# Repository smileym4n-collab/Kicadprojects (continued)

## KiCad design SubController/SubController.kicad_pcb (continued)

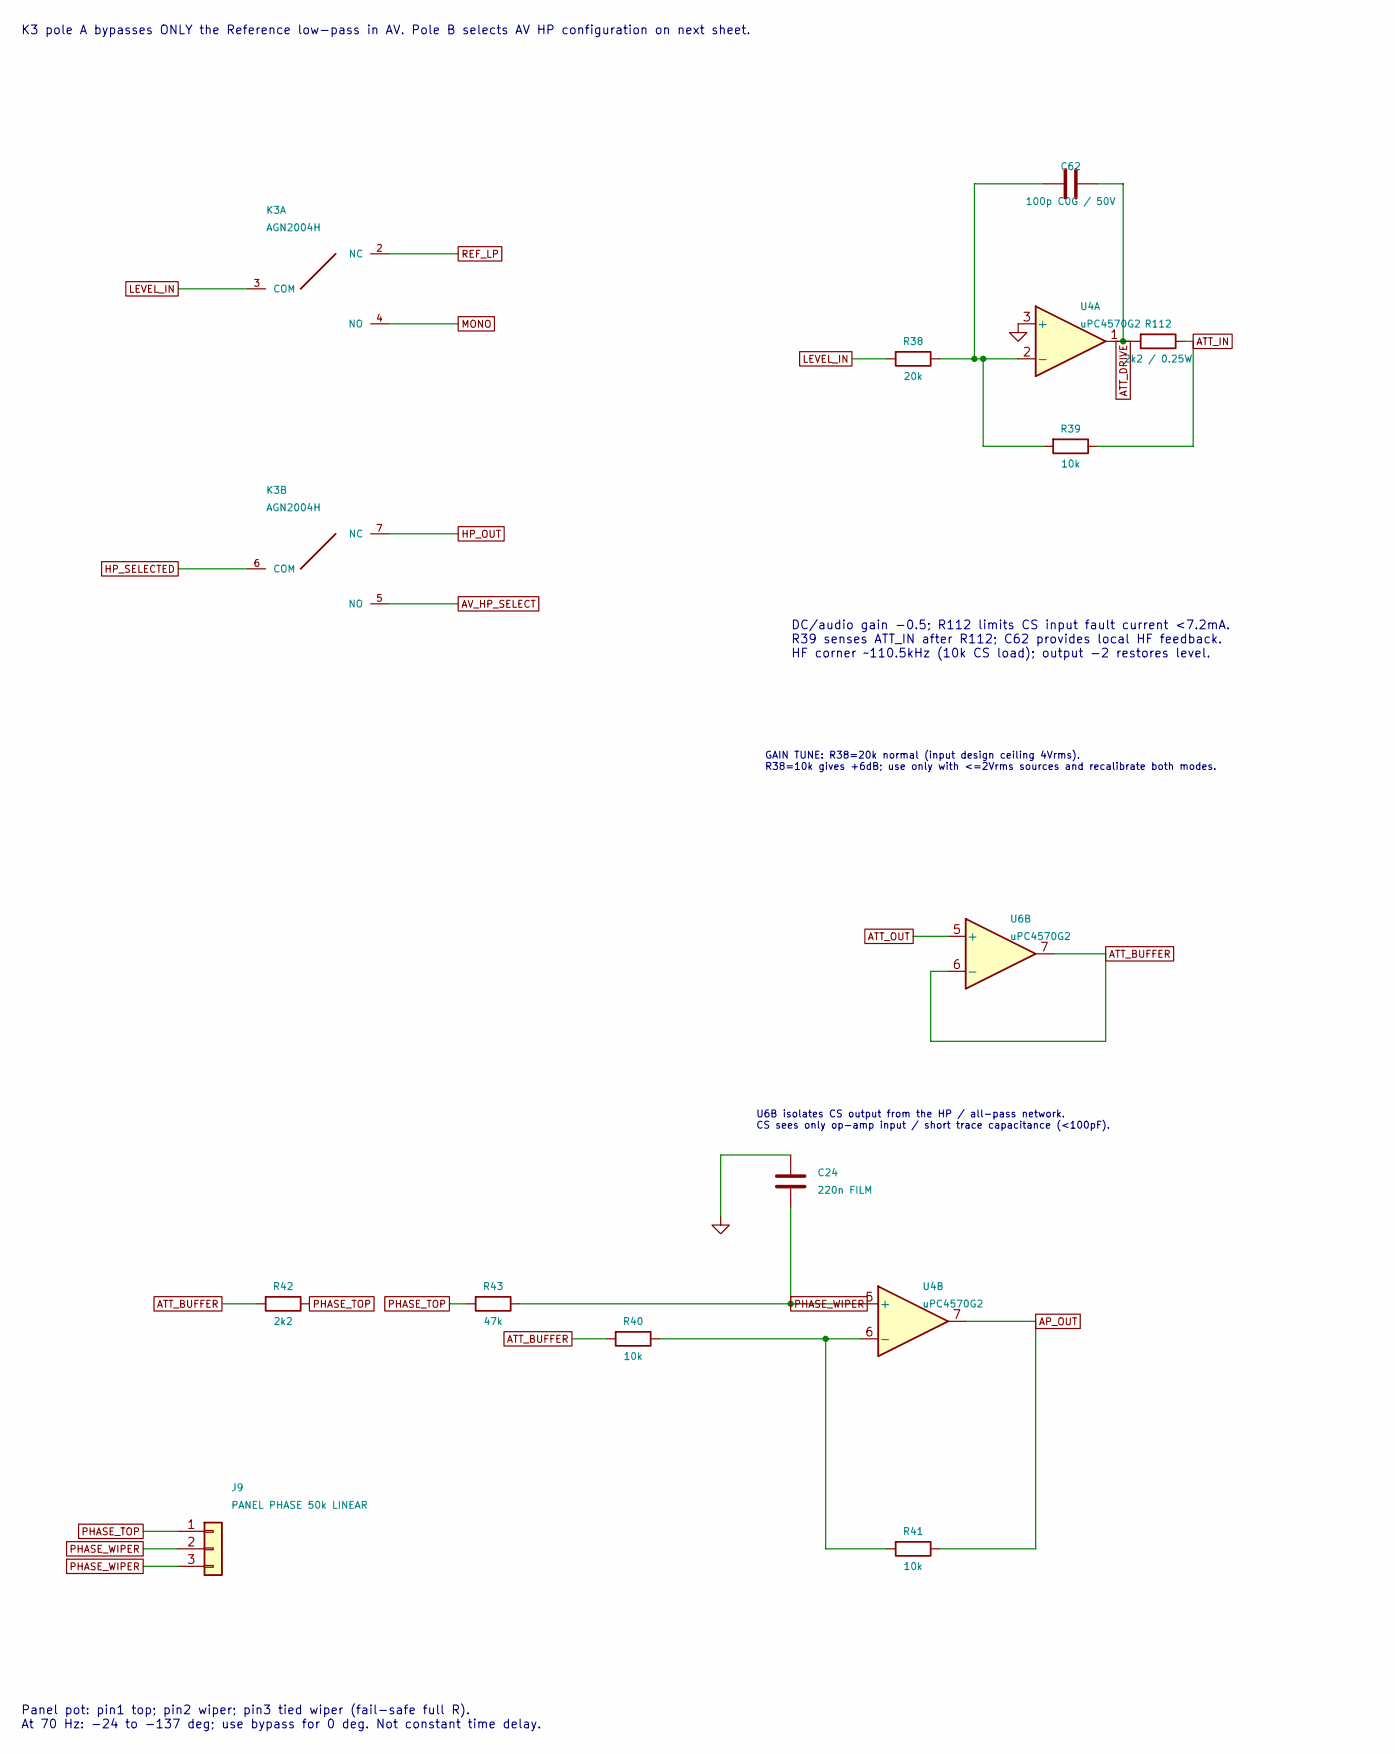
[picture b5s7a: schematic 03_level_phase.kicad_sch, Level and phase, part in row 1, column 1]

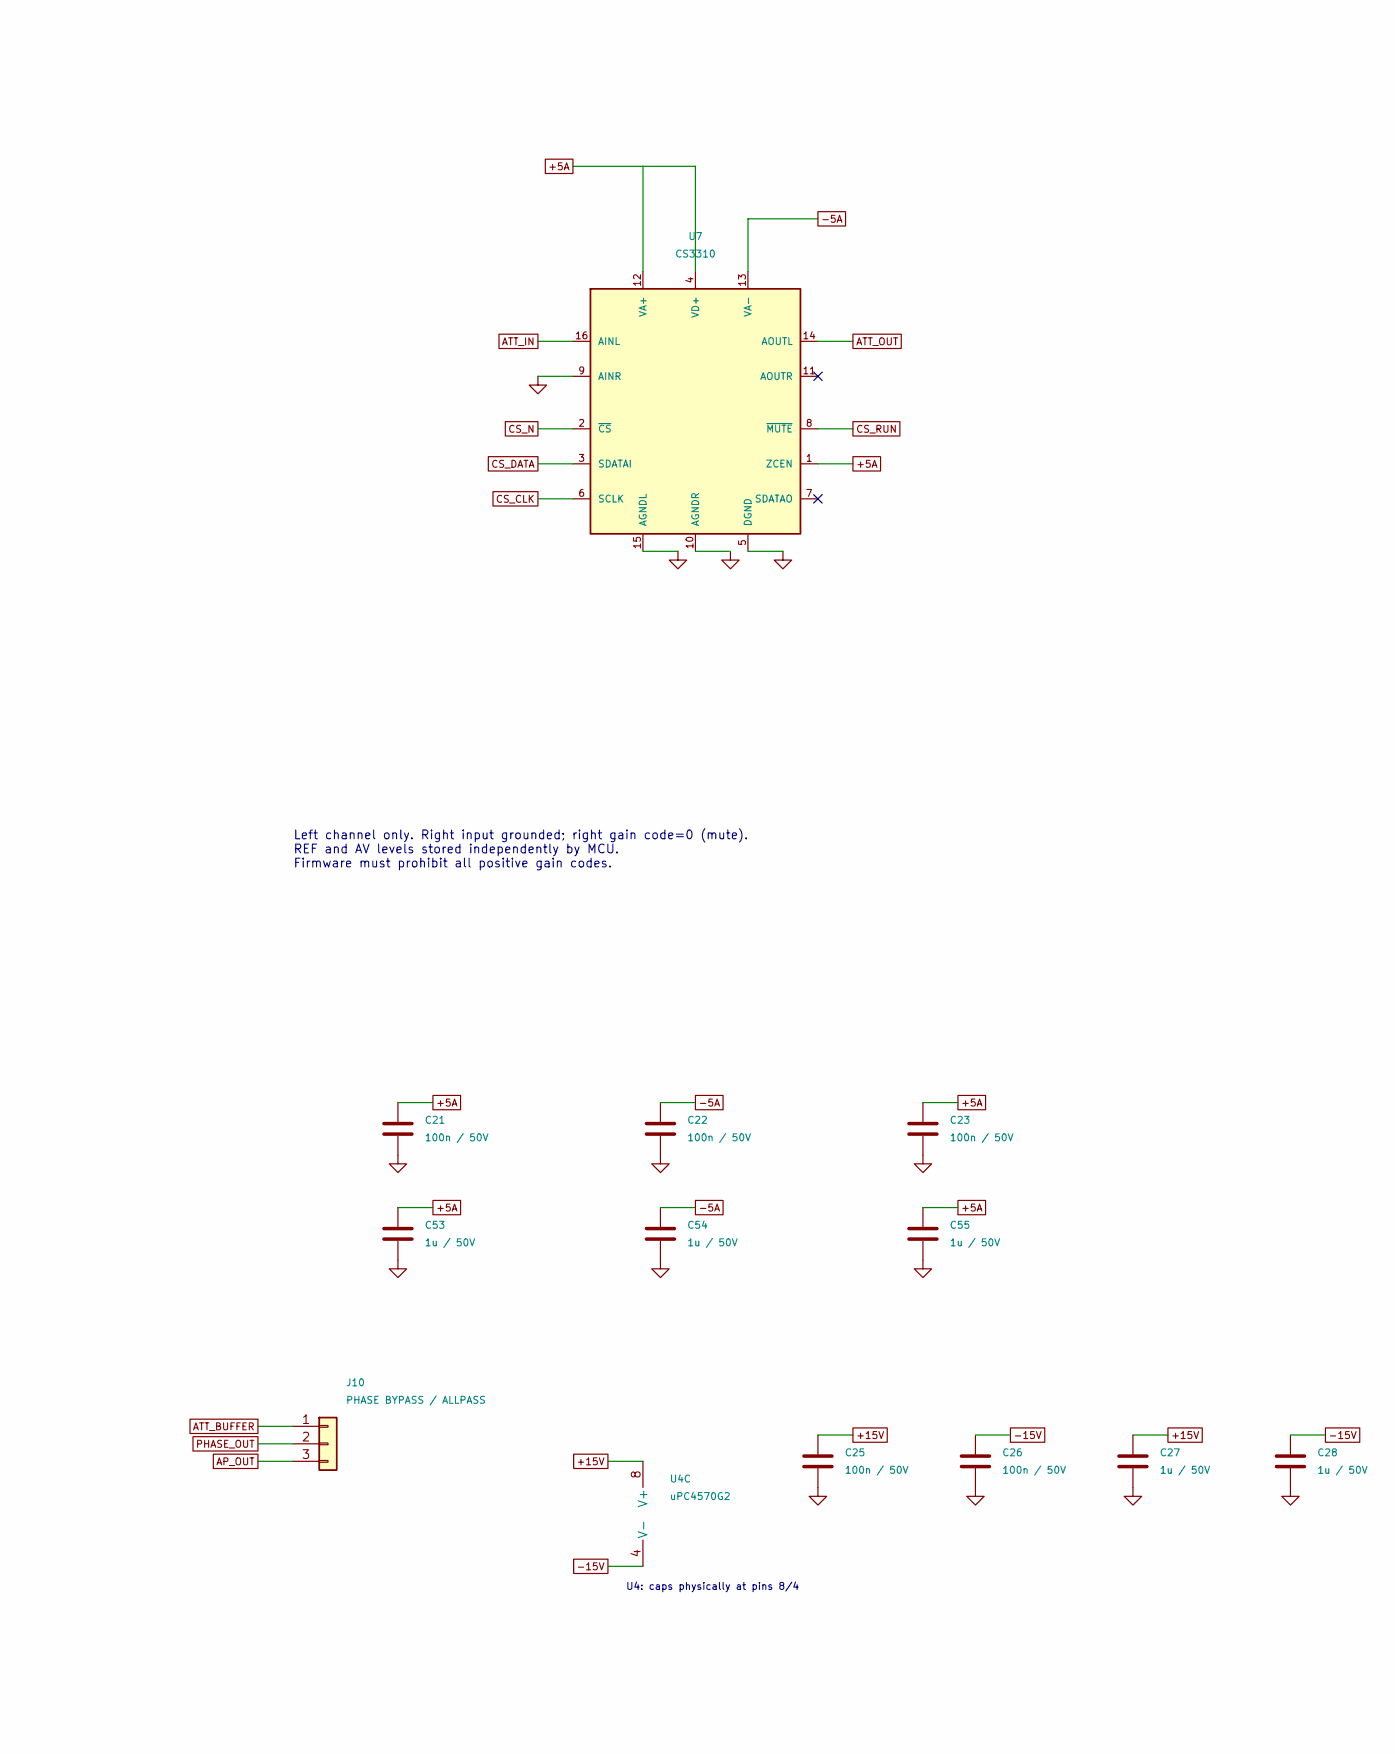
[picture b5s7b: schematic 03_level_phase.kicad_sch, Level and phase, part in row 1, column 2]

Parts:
C21, C22, C23, C25, C26: 100n / 50V; C_1206_3216Metric
C24: 220n FILM; Film_7.2x2.5mm_P5.00mm
C27, C28, C53, C54, C55: 1u / 50V; C_1206_3216Metric
C62: 100p C0G / 50V; C_0805_2012Metric
J9: PANEL PHASE 50k LINEAR; PinHeader_1x03_P2.54mm_Vertical
J10: PHASE BYPASS / ALLPASS; PinHeader_1x03_P2.54mm_Vertical
K3: AGN2004H; Relay_DPDT_Panasonic_AGN2004H
R38: 20k; R_0805_2012Metric
R39, R40, R41: 10k; R_0805_2012Metric
R42: 2k2; R_0805_2012Metric
R43: 47k; R_0805_2012Metric
R112: 2k2 / 0.25W; R_0805_2012Metric
U4, U6: uPC4570G2; SOP-8_uPC4570G2_4.4x5.2mm_P1.27mm
U7: CS3310; SOIC-16W_7.5x10.3mm_P1.27mm

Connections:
+5A: C21.1, C23.1, C53.1, C55.1, U7.1 (ZCEN), U7.4 (VD+), U7.12 (VA+); also elsewhere on the board
+15V: C25.1, C27.1, U4.8 (V+); also elsewhere on the board
-5A: C22.1, C54.1, U7.13 (VA-); also elsewhere on the board
-15V: C26.1, C28.1, U4.4 (V-); also elsewhere on the board
AP_OUT: J10.3, R41.1, U4.7
ATT_BUFFER: J10.1, R40.2, R42.2, U6.6 (-), U6.7
ATT_DRIVE: C62.1, R112.2, U4.1
ATT_IN: R39.1, R112.1, U7.16 (AINL)
ATT_OUT: U6.5 (+), U7.14 (AOUTL)
AV_HP_SELECT: K3.5 (NO); also elsewhere on the board
CS_CLK: U7.6 (SCLK); also elsewhere on the board
CS_DATA: U7.3 (SDATAI); also elsewhere on the board
CS_N: U7.2 (~CS); also elsewhere on the board
CS_RUN: U7.8 (~MUTE); also elsewhere on the board
GND: C21.2, C22.2, C23.2, C24.1, C25.2, C26.2, C27.2, C28.2, C53.2, C54.2, C55.2, U4.3 (+), U7.5 (DGND), U7.9 (AINR), U7.10 (AGNDR), U7.15 (AGNDL); also elsewhere on the board
HP_OUT: K3.7 (NC); also elsewhere on the board
HP_SELECTED: K3.6 (COM); also elsewhere on the board
LEVEL_IN: K3.3 (COM), R38.2
MONO: K3.4 (NO); also elsewhere on the board
unnamed: C62.2, R38.1, R39.2, U4.2 (-)
unnamed: R40.1, R41.2, U4.6 (-)
PHASE_OUT: J10.2; also elsewhere on the board
PHASE_TOP: J9.1, R42.1, R43.2
PHASE_WIPER: C24.2, J9.2, J9.3, R43.1, U4.5 (+)
REF_LP: K3.2 (NC); also elsewhere on the board

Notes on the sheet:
Panel pot: pin1 top; pin2 wiper; pin3 tied wiper (fail-safe full R). At 70 Hz: -24 to -137 deg; use bypass for 0 deg. Not constant time delay.
DC/audio gain -0.5; R112 limits CS input fault current <7.2mA. R39 senses ATT_IN after R112; C62 provides local HF feedback. HF corner ~110.5kHz (10k CS load); output -2 restores level.
K3 pole A bypasses ONLY the Reference low-pass in AV. Pole B selects AV HP configuration on next sheet.
U6B isolates CS output from the HP / all-pass network. CS sees only op-amp input / short trace capacitance (<100pF).
U4: caps physically at pins 8/4
Left channel only. Right input grounded; right gain code=0 (mute). REF and AV levels stored independently by MCU. Firmware must prohibit all positive gain codes.
GAIN TUNE: R38=20k normal (input design ceiling 4Vrms). R38=10k gives +6dB; use only with <=2Vrms sources and recalibrate both modes.

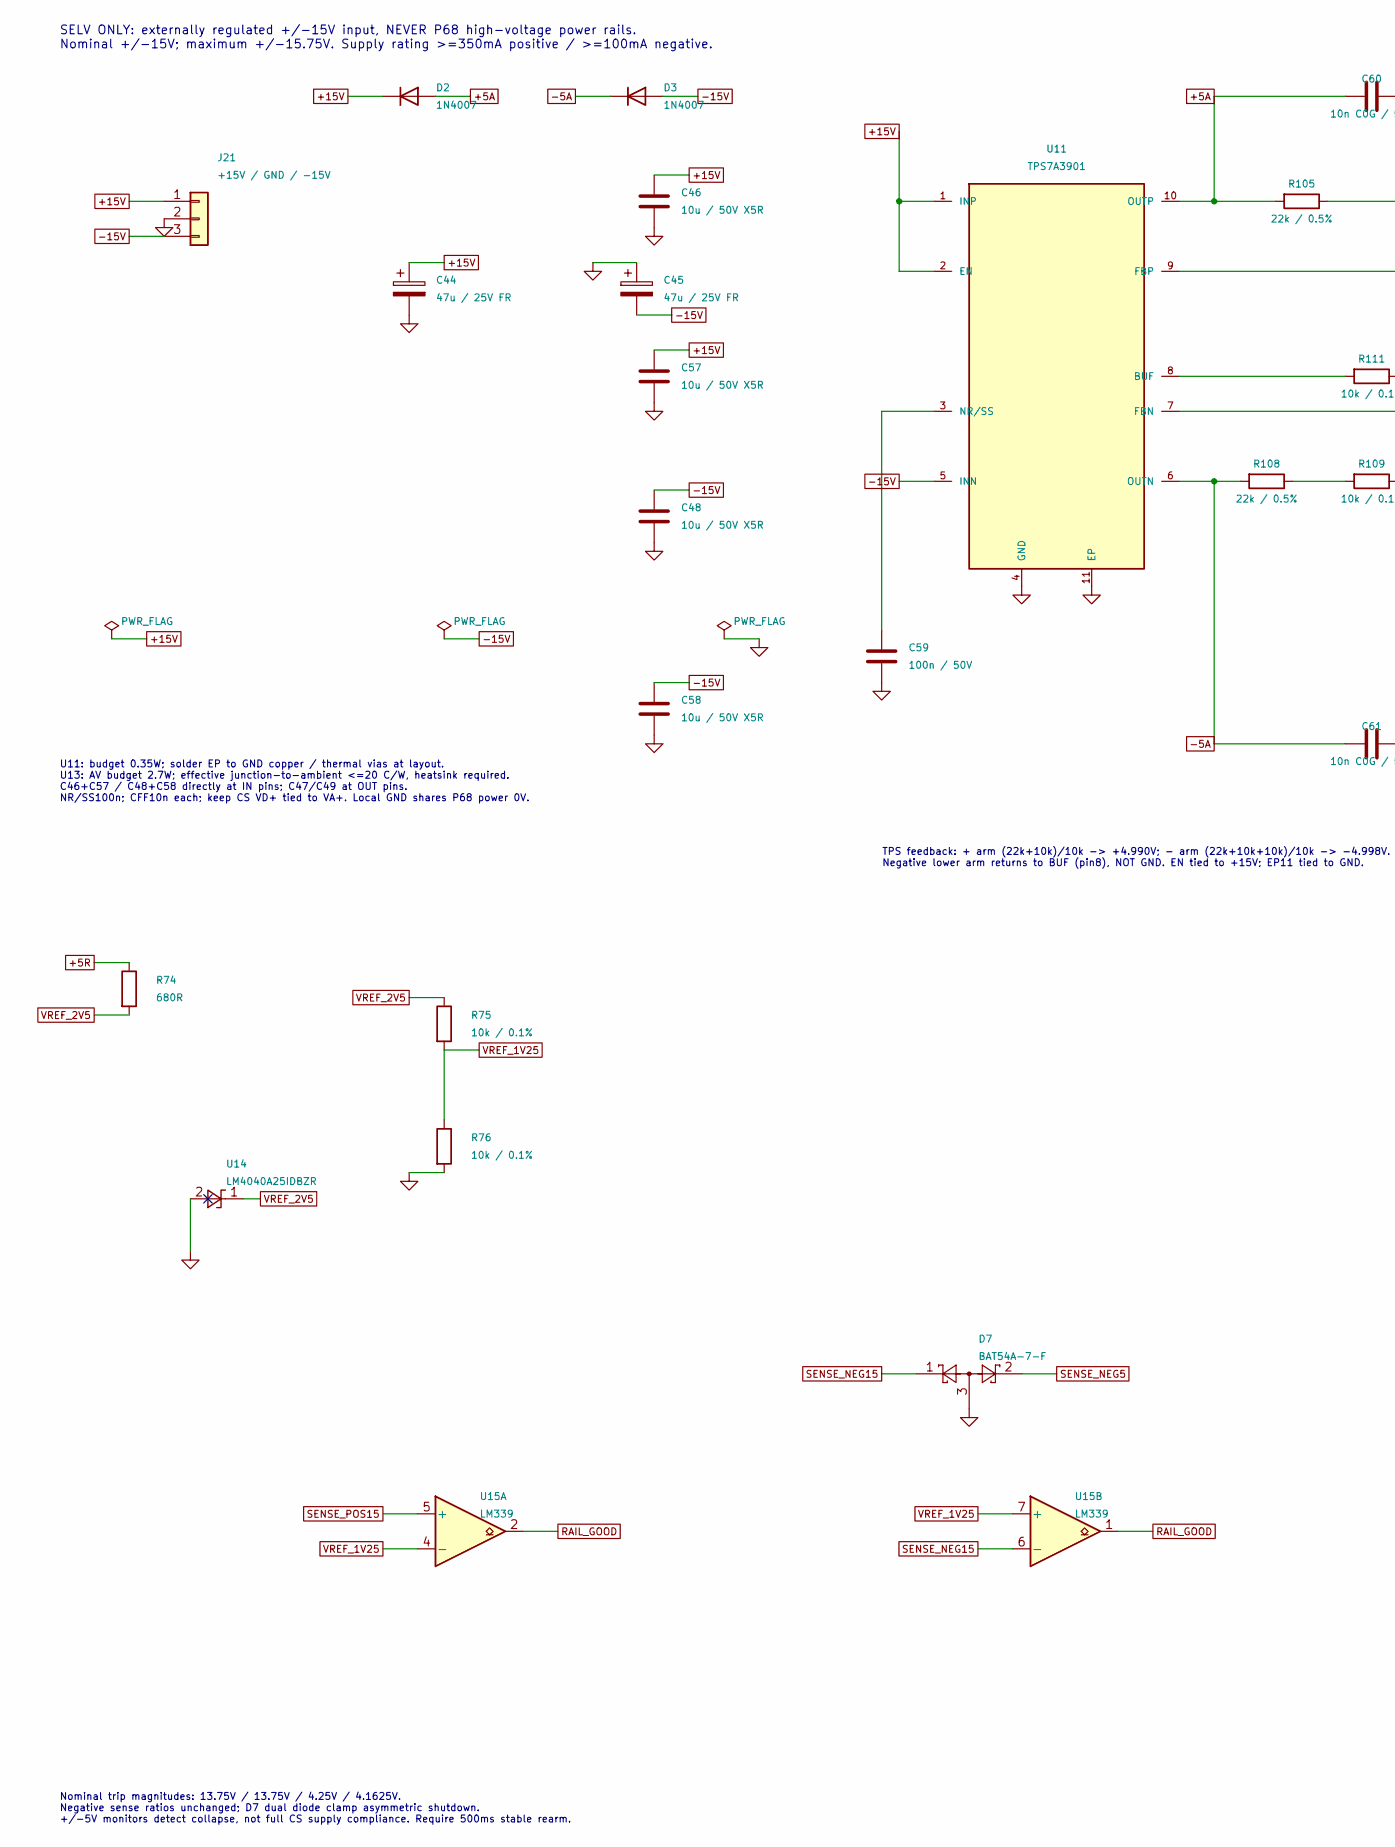
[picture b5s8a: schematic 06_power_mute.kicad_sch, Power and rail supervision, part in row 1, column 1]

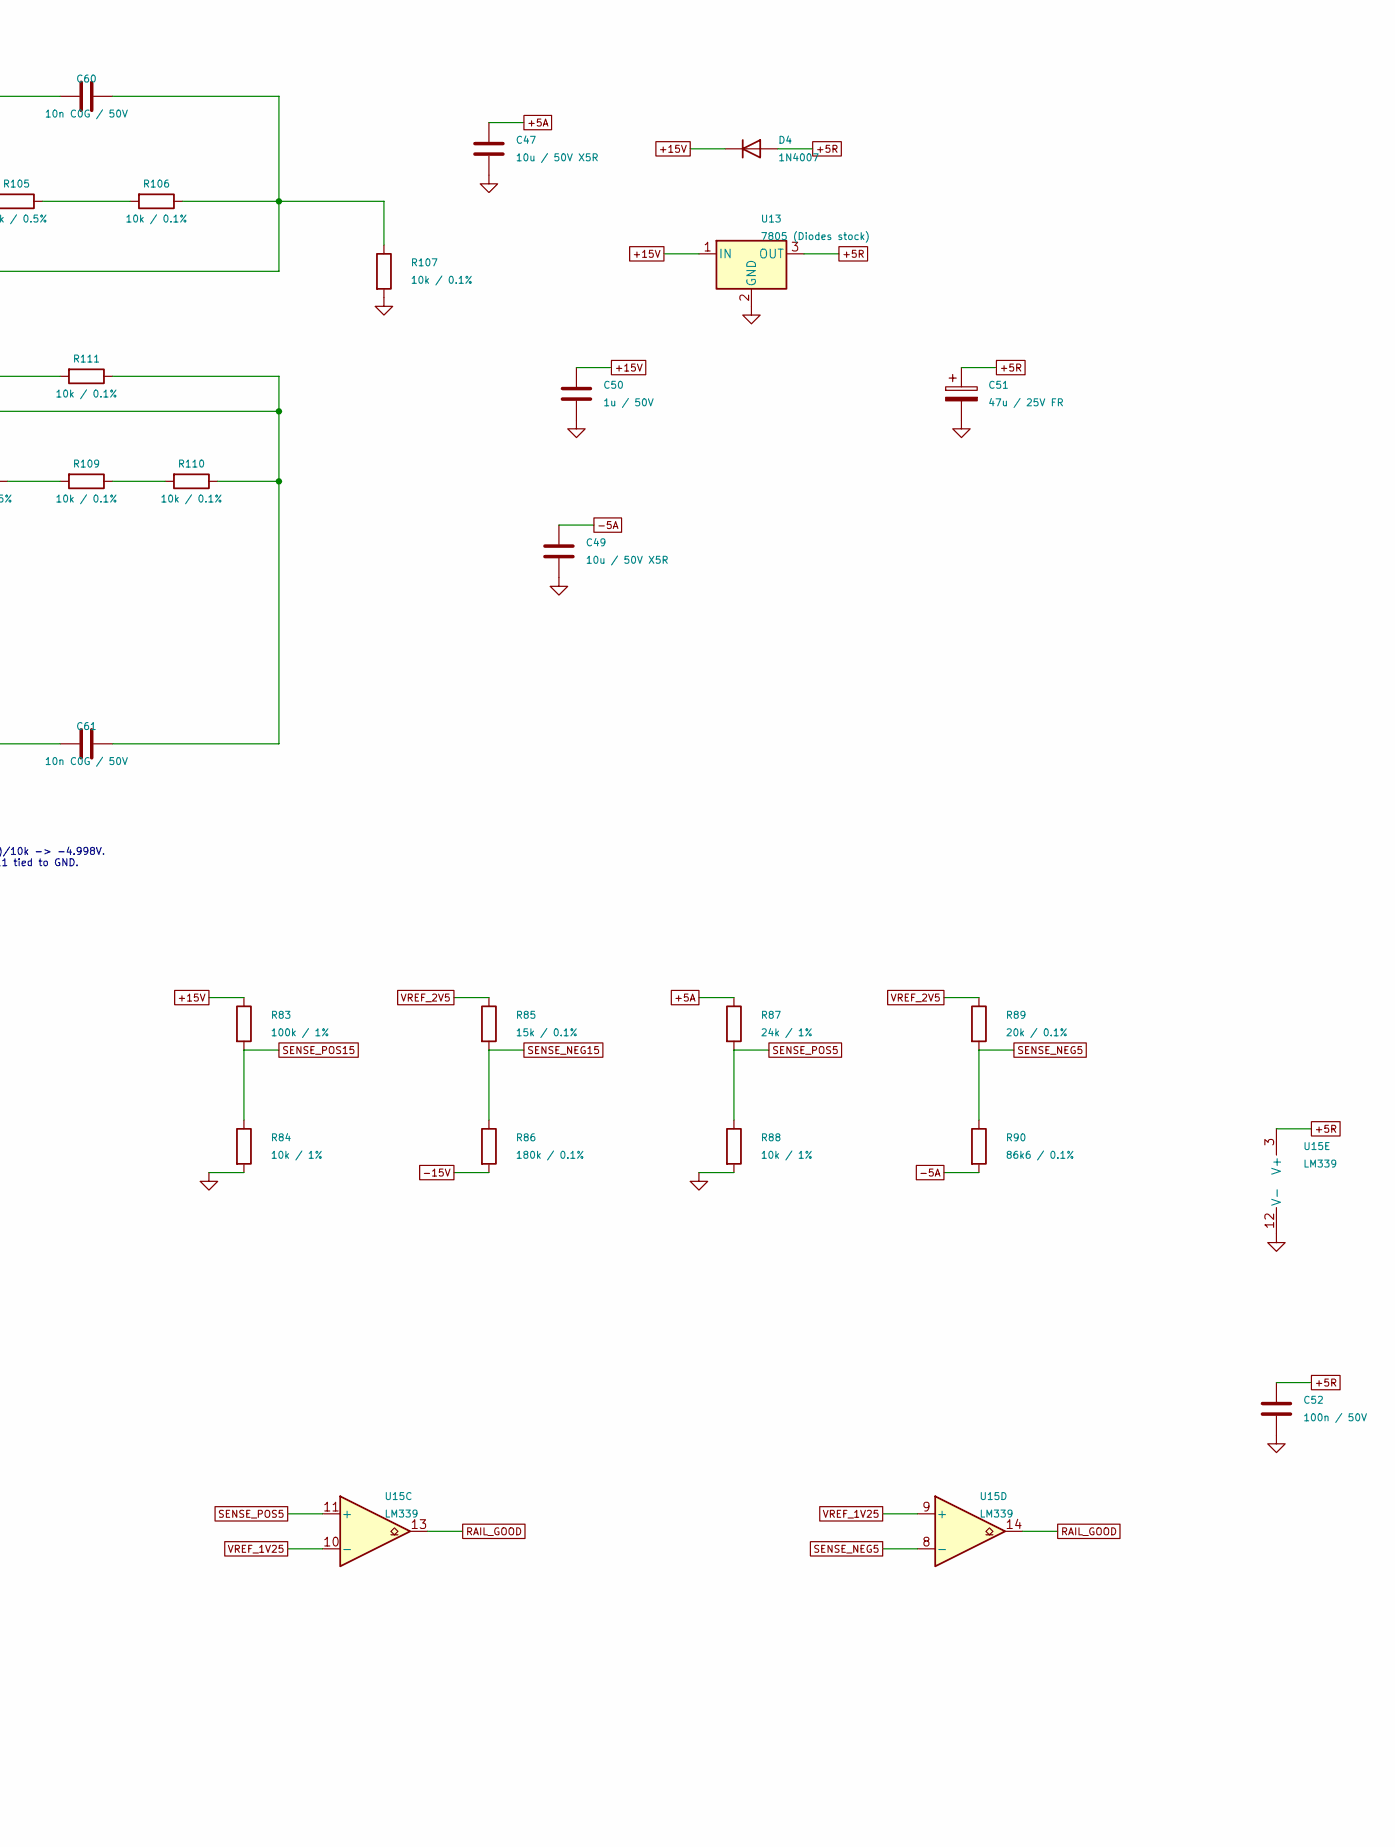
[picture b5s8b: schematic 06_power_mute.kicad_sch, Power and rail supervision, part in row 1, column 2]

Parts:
C44, C45, C51: 47u / 25V FR; CP_Radial_D5.0mm_P2.50mm
C46, C47, C48, C49, C57, C58: 10u / 50V X5R; C_1206_3216Metric
C50: 1u / 50V; C_1206_3216Metric
C52, C59: 100n / 50V; C_1206_3216Metric
C60, C61: 10n C0G / 50V; C_0805_2012Metric
D2, D3, D4: 1N4007; D_DO-41_SOD81_P10.16mm_Horizontal
D7: BAT54A-7-F; SOT-23
J21: +15V / GND / -15V; PinHeader_1x03_P2.54mm_Vertical
R74: 680R; R_0805_2012Metric
R75, R76, R106, R107, R109, R110, R111: 10k / 0.1%; R_0805_2012Metric
R83: 100k / 1%; R_0805_2012Metric
R84, R88: 10k / 1%; R_0805_2012Metric
R85: 15k / 0.1%; R_0805_2012Metric
R86: 180k / 0.1%; R_0805_2012Metric
R87: 24k / 1%; R_0805_2012Metric
R89: 20k / 0.1%; R_0805_2012Metric
R90: 86k6 / 0.1%; R_0805_2012Metric
R105, R108: 22k / 0.5%; R_0805_2012Metric
U11: TPS7A3901; TPS7A3901_DSC0010J_WSON10
U13: 7805 (Diodes stock); TO-220-3_Vertical
U14: LM4040A25IDBZR; SOT-23
U15: LM339; SOIC-14_3.9x8.7mm_P1.27mm

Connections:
+5A: C47.1, C60.2, D2.2 (A), R87.1, R105.2, U11.10 (OUTP); also elsewhere on the board
+5R: C51.1, C52.1, D4.2 (A), R74.1, U13.3 (OUT), U15.3 (V+); also elsewhere on the board
+15V: C44.1, C46.1, C50.1, C57.1, D2.1 (K), D4.1 (K), J21.1, R83.1, U11.1 (INP), U11.2 (EN), U13.1 (IN); also elsewhere on the board
-5A: C49.1, C61.2, D3.1 (K), R90.2, R108.2, U11.6 (OUTN); also elsewhere on the board
-15V: C45.2, C48.1, C58.1, D3.2 (A), J21.3, R86.2, U11.5 (INN); also elsewhere on the board
GND: C44.2, C45.1, C46.2, C47.2, C48.2, C49.2, C50.2, C51.2, C52.2, C57.2, C58.2, C59.2, D7.3, J21.2, R76.2, R84.2, R88.2, R107.2, U11.4 (GND), U11.11 (EP), U13.2 (GND), U14.2 (A), U15.12 (V-); also elsewhere on the board
unnamed: R105.1, R106.2
unnamed: R108.1, R109.2
unnamed: R109.1, R110.2
unnamed: R111.2, U11.8 (BUF)
unnamed: C61.1, R110.1, R111.1, U11.7 (FBN)
unnamed: C60.1, R106.1, R107.1, U11.9 (FBP)
unnamed: C59.1, U11.3 (NR/SS)
RAIL_GOOD: U15.1, U15.2, U15.13, U15.14; also elsewhere on the board
SENSE_NEG5: D7.2, R89.2, R90.1, U15.8 (-)
SENSE_NEG15: D7.1, R85.2, R86.1, U15.6 (-)
SENSE_POS5: R87.2, R88.1, U15.11 (+)
SENSE_POS15: R83.2, R84.1, U15.5 (+)
VREF_1V25: R75.2, R76.1, U15.4 (-), U15.7 (+), U15.9 (+), U15.10 (-)
VREF_2V5: R74.2, R75.1, R85.1, R89.1, U14.1 (K)

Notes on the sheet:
U11: budget 0.35W; solder EP to GND copper / thermal vias at layout. U13: AV budget 2.7W; effective junction-to-ambient <=20 C/W, heatsink required. C46+C57 / C48+C58 directly at IN pins; C47/C49 at OUT pins. NR/SS100n; CFF10n each; keep CS VD+ tied to VA+. Local GND shares P68 power 0V.
TPS feedback: + arm (22k+10k)/10k -> +4.990V; - arm (22k+10k+10k)/10k -> -4.998V. Negative lower arm returns to BUF (pin8), NOT GND. EN tied to +15V; EP11 tied to GND.
Nominal trip magnitudes: 13.75V / 13.75V / 4.25V / 4.1625V. Negative sense ratios unchanged; D7 dual diode clamp asymmetric shutdown. +/-5V monitors detect collapse, not full CS supply compliance. Require 500ms stable rearm.
SELV ONLY: externally regulated +/-15V input, NEVER P68 high-voltage power rails. Nominal +/-15V; maximum +/-15.75V. Supply rating >=350mA positive / >=100mA negative.

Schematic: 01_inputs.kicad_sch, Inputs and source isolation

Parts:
C1, C2, C64, C65: 100p C0G / 50V; C_0805_2012Metric
C3, C4, C7, C8: 100nF; C_1206_3216Metric
C5, C6, C9, C10: 1uF; C_1206_3216Metric
J1: REF LEFT; JST_XH_B2B-XH-A_1x02_P2.50mm_Vertical
J2: REF RIGHT; JST_XH_B2B-XH-A_1x02_P2.50mm_Vertical
J3: MARANTZ LFE; JST_XH_B2B-XH-A_1x02_P2.50mm_Vertical
K1, K2, K5: AGN2004H; Relay_DPDT_Panasonic_AGN2004H
R1, R2, R3, R4, R119, R120, R121, R122: 47k / 0.1%; R_0805_2012Metric
R5, R6: 22K; R_0805_2012Metric
R7, R8, R9: 10K; R_0805_2012Metric
TP7: GND; TestPoint_Pad_D1.5mm
TP8: BUF_L; TestPoint_Pad_D1.5mm
TP9: BUF_R; TestPoint_Pad_D1.5mm
TP10: MONO; TestPoint_Pad_D1.5mm
U1, U2: uPC4570G2; SOP-8_uPC4570G2_4.4x5.2mm_P1.27mm

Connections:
+15V: C3.1, C5.1, C7.1, C9.1, U1.8 (V+), U2.8 (V+); also elsewhere on the board
-15V: C4.1, C6.1, C8.1, C10.1, U1.4 (V-), U2.4 (V-); also elsewhere on the board
BUF_L: C64.1, R5.2, R119.1, TP8.1 (1_1), U1.1
BUF_R: C65.1, R6.2, R121.1, TP9.1 (1_1), U1.7
GND: C1.2, C2.2, C3.2, C4.2, C5.2, C6.2, C7.2, C8.2, C9.2, C10.2, K5.2 (NC), K5.7 (NC), R2.2, R4.2, TP7.1 (1_1), U2.3 (+), U2.5 (+); also elsewhere on the board
LFE: J3.1, K1.4 (NO), K1.5 (NO)
LFE_RETURN: J3.2, K2.4 (NO)
LIVE_L: K5.3 (COM), R1.2
LIVE_R: K5.6 (COM), R3.2
MONO: R9.1, TP10.1 (1_1), U2.7; also elsewhere on the board
unnamed: C1.1, R1.1, R2.1, U1.3 (+)
unnamed: C64.2, R119.2, R120.1, U1.2 (-)
unnamed: C2.1, R3.1, R4.1, U1.5 (+)
unnamed: C65.2, R121.2, R122.1, U1.6 (-)
unnamed: R5.1, R6.1, R7.2, U2.2 (-)
unnamed: R8.1, R9.2, U2.6 (-)
REF_L: J1.1, K1.2 (NC)
REF_R: J2.1, K1.7 (NC)
REF_RETURN: J1.2, J2.2, K2.2 (NC)
SEL_L: K1.3 (COM), K5.4 (NO)
SEL_R: K1.6 (COM), K5.5 (NO)
SOURCE_RETURN: K2.3 (COM), R120.2, R122.2
SUM_INV: R7.1, R8.2, U2.1

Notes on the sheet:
U2: caps physically at pins 8/4
U1: caps physically at pins 8/4
MONO = (10/22)(L+R); AV = (20/22)LFE, after differential receivers. No direct L/R connection. Main speakers remain full range.
U1 differential receivers: Vout = SIGNAL - SOURCE_RETURN (DC gain1). 47k matched ratios; REF input ~94k/channel, LFE ~47k. Return is sensed, not bonded. C1/C64 and C2/C65: matched 100p C0G; differential RF pole ~33.9kHz. 0.1% resistors; select capacitor pairs within 2% for common-mode rejection.
TP8/9: selected REF L/R buffers; both carry LFE in AV. Probe inactive RCA returns only with an isolated/differential instrument.
RCA shells MUST be insulated from plate/chassis. Inactive source has no bias / ESD path to board GND.
NC = REFERENCE; energised = AV. K1/K2 switch while K4 muted. Coils on driver sheet.
K5 OFF grounds buffer inputs; powered sources are disconnected. K5 and K4 share RUN. Connect at CS code0, wait 2s, then fade up.
K2A selects SOURCE_RETURN for differential input sensing. K2B unused. Reference L/R returns share REF_RETURN before the relay. Never bond SOURCE_RETURN to GND or chassis.

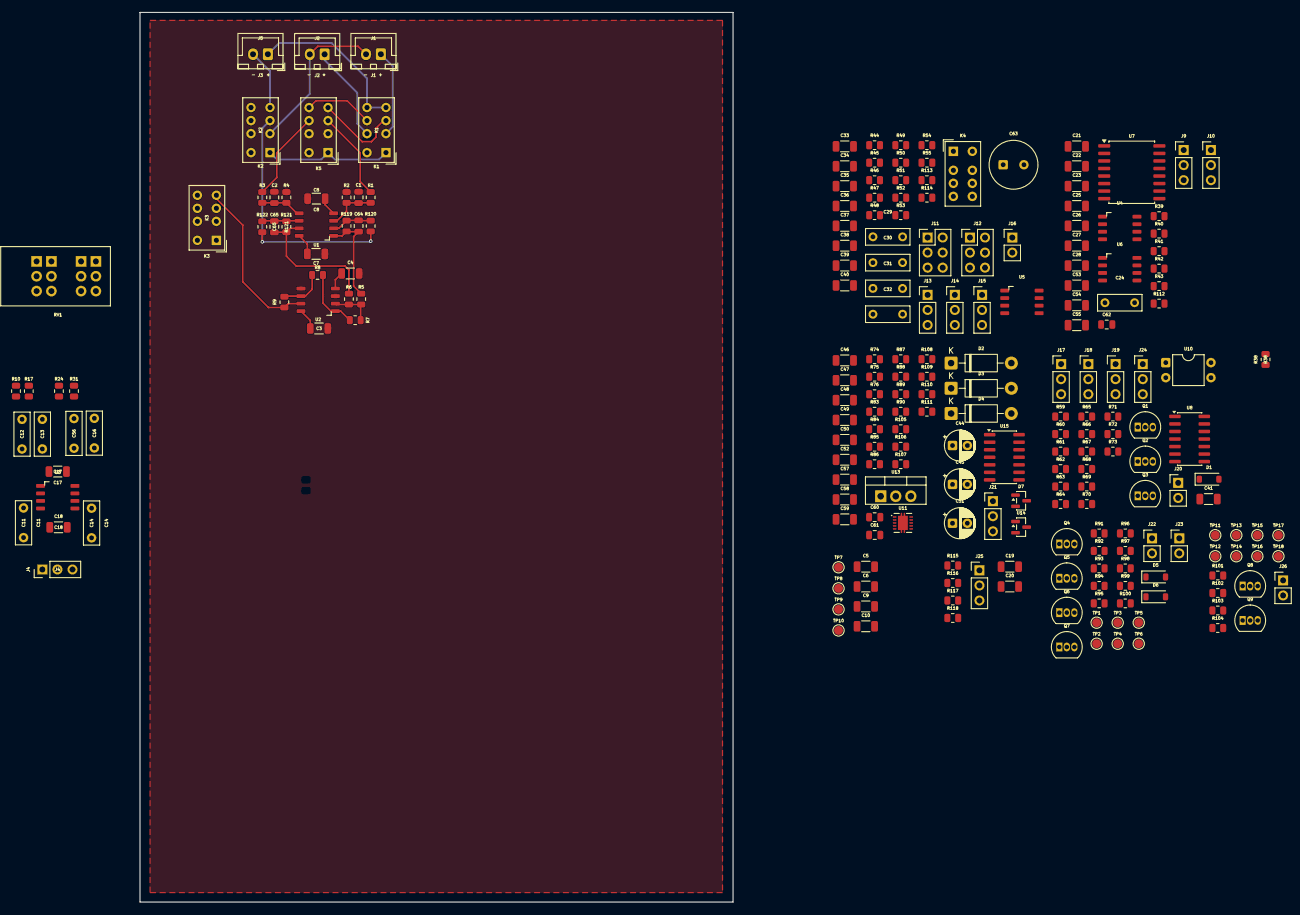
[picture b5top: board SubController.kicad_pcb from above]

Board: 2 copper layers, 100.0 x 150.0 mm, 226 parts (0 on the bottom side), 119 nets.

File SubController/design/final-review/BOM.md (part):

# Final schematic BOM — revision B, 8 October 2026

226 component references, including test-point pads. Generated from the final KiCad netlist. Inventory was read live; nothing was reserved or decremented. Stock markings/package checks remain as stated below.

## Inventory allocation

| ID | Exact recorded part | Required / stock | Buy shortage | Location |
|---:|---|---:|---:|---|
| 87 | RR1220P-471-D | 1 / 15 | 0 | SMD Parts |
| 88 | 0805N103J500CT | 2 / 38 | 0 | SMD Parts |
| 95 | EEUFR1E470H | 3 / 50 | 0 | Parts drawer 2 |
| 109 | 7805 | 1 / 17 | 0 | Voltage Regulator drawer |
| 124 | 1N4007 | 3 / 62 | 0 | Parts drawer 2 |
| 157 | C1206C104K5RACTU | 18 / 129 | 0 | SMD Parts |
| 181 | CL31B105KBHNFNE | 16 / 50 | 0 | SMD Parts |
| 197 | CL21C101JBANNNC | 5 / 100 | 0 | SMD Parts |
| 209 | 100R Thin Film | 2 / 26 | 0 | SMD Parts |
| 220 | 680R Thin Film | 1 / 39 | 0 | SMD Parts |
| 224 | 1K Thin Film | 1 / 42 | 0 | SMD Parts |
| 235 | 15K Thin Film | 4 / 22 | 0 | SMD Parts |
| 242 | 100K Thin Film | 3 / 70 | 0 | SMD Parts |
| 294 | ATTiny1614 | 1 / 4 | 0 | SMD Parts |
| 375 | 10K Thin Film | 34 / 50 | 0 | SMD Parts |
| 376 | 47K Thin Film | 13 / 30 | 0 | SMD Parts |
| 414 | 220n Film | 11 / 8 | 3 | Parts Drawer 2 |
| 461 | BC337 | 9 / 19 | 0 | not recorded |
| 493 | RMCF0805FT4K70 | 4 / 100 | 0 | SMD Parts |
| 500 | TPS7A3901 | 1 / 2 | 0 | SMD Parts |
| 503 | RMCF0805FT2K20 | 2 / 100 | 0 | SMD Parts |
| 505 | CL31A106KBHNNNE | 6 / 10 | 0 | SMD Parts |
| 510 | 1N4148W | 3 / 85 | 0 | Parts drawer 2 |
| 511 | RR1220P-223-D | 5 / 50 | 0 | SMD Parts |
| 588 | LM339 | 1 / 2 | 0 | SMD Parts |
| 595 | CS3310 | 1 / 5 | 0 | not recorded |
| 615 | 4570 | 6 / 22 | 0 | SMD Parts |
| 616 | AGN2004H | 5 / 6 | 0 | not recorded |

## Complete grouped BOM

| References | Value | Qty | Status / inventory | Footprint | Qualification |
|---|---|---:|---|---|---|
| C1, C2, C62, C64, C65 | 100p C0G / 50V | 5 | OWNED / 197 | `Capacitor_SMD:C_0805_2012Metric` | 50V C0G, 2012 metric. Match C1/C64 and C2/C65 within 2%; C62 compensation. |
| C3, C4, C7, C8, C17, C18 | 100nF | 6 | OWNED / 157 | `Capacitor_SMD:C_1206_3216Metric` | 50V X7R supply bypass, 3216 metric. |
| C5, C6, C9, C10, C19, C20 | 1uF | 6 | OWNED / 181 | `Capacitor_SMD:C_1206_3216Metric` | 50V X7R supply bypass, 3216 metric. |
| C11, C12, C13, C14, C16 | 220n FILM / 63V | 5 | OWNED / 414 | `Capacitor_THT:C_Rect_L7.2mm_W2.5mm_P5.00mm_FKS2_FKP2_MKS2_MKP2` | 63V 5% film, body <=7.2x2.5mm, pitch5mm; measure stock lead pitch/dielectric. Buy shortage as KEMET 82DC3220AA60J (legacy R82DC3220AA60J), polyester film; select matching pairs. |
| C21, C22, C23, C25, C26, C33, C34, C37, C38, C41, C52, C59 | 100n / 50V | 12 | OWNED / 157 | `Capacitor_SMD:C_1206_3216Metric` | 50V X7R supply bypass, 3216 metric. |
| C24, C29, C30 | 220n FILM | 3 | OWNED / 414 | `SubController:Film_7.2x2.5mm_P5.00mm` | 63V 5% film, body <=7.2x2.5mm, pitch5mm; measure stock lead pitch/dielectric. Buy shortage as KEMET 82DC3220AA60J (legacy R82DC3220AA60J), polyester film; select matching pairs. |
| C27, C28, C35, C36, C39, C40, C50, C53, C54, C55 | 1u / 50V | 10 | OWNED / 181 | `Capacitor_SMD:C_1206_3216Metric` | 50V X7R supply bypass, 3216 metric. |
| C31, C32 | 220n FILM | 2 | SHORTAGE / BUY / 414 | `SubController:Film_7.2x2.5mm_P5.00mm` | 63V 5% film, body <=7.2x2.5mm, pitch5mm; measure stock lead pitch/dielectric. Buy shortage as KEMET 82DC3220AA60J (legacy R82DC3220AA60J), polyester film; select matching pairs. |
| C44, C45, C51 | 47u / 25V FR | 3 | OWNED / 95 | `Capacitor_THT:CP_Radial_D5.0mm_P2.50mm` | 25V Panasonic FR; verify formed lead spacing against 2.5mm footprint. |
| C46, C47, C48, C49, C57, C58 | 10u / 50V X5R | 6 | OWNED / 505 | `Capacitor_SMD:C_1206_3216Metric` | 50V X5R, 3216 metric; supply use only. Verify effective capacitance at 15V against regulator requirement. |
| C56 | 220n FILM / 63V | 1 | SHORTAGE / BUY / 414 | `Capacitor_THT:C_Rect_L7.2mm_W2.5mm_P5.00mm_FKS2_FKP2_MKS2_MKP2` | 63V 5% film, body <=7.2x2.5mm, pitch5mm; measure stock lead pitch/dielectric. Buy shortage as KEMET 82DC3220AA60J (legacy R82DC3220AA60J), polyester film; select matching pairs. |
| C60, C61 | 10n C0G / 50V | 2 | OWNED / 88 | `Capacitor_SMD:C_0805_2012Metric` | 50V C0G, 2012 metric; TPS feed-forward. |
| C63 | 10u / 50V BIPOLAR | 1 | NEW / SOURCE | `SubController:C_NP_Radial_D8.0mm_P3.50mm` | Nichicon UES1H100MPM; 10uF 50V bipolar; diameter8mm height11.5mm pitch3.5mm. |
| D1, D5, D6 | 1N4148W | 3 | OWNED / 510 | `Diode_SMD:D_SOD-123` |  |
| D2, D3, D4 | 1N4007 | 3 | OWNED / 124 | `Diode_THT:D_DO-41_SOD81_P10.16mm_Horizontal` |  |
| D7 | BAT54A-7-F | 1 | NEW / SOURCE | `Package_TO_SOT_SMD:SOT-23` | Diodes BAT54A-7-F common-anode dual Schottky: pins1/2 cathodes,3 common anode. |
| J1 | REF LEFT | 1 | MECHANICAL / SOURCE | `Connector_JST:JST_XH_B2B-XH-A_1x02_P2.50mm_Vertical` | Preserved connector family. Fit exact matching housing: JST-XH2.50mm is not Multicomp2.54mm. Headers/jumpers and panel controls must be checked separately. |
| J2 | REF RIGHT | 1 | MECHANICAL / SOURCE | `Connector_JST:JST_XH_B2B-XH-A_1x02_P2.50mm_Vertical` | Preserved connector family. Fit exact matching housing: JST-XH2.50mm is not Multicomp2.54mm. Headers/jumpers and panel controls must be checked separately. |
| J3 | MARANTZ LFE | 1 | MECHANICAL / SOURCE | `Connector_JST:JST_XH_B2B-XH-A_1x02_P2.50mm_Vertical` | Preserved connector family. Fit exact matching housing: JST-XH2.50mm is not Multicomp2.54mm. Headers/jumpers and panel controls must be checked separately. |
| J4 | SLOPE: 1-2=12 / 2-3=24 | 1 | MECHANICAL / SOURCE | `Connector_PinHeader_2.54mm:PinHeader_1x03_P2.54mm_Vertical` | Preserved connector family. Fit exact matching housing: JST-XH2.50mm is not Multicomp2.54mm. Headers/jumpers and panel controls must be checked separately. |
| J9 | PANEL PHASE 50k LINEAR | 1 | MECHANICAL / SOURCE | `Connector_PinHeader_2.54mm:PinHeader_1x03_P2.54mm_Vertical` | Preserved connector family. Fit exact matching housing: JST-XH2.50mm is not Multicomp2.54mm. Headers/jumpers and panel controls must be checked separately. |
| J10 | PHASE BYPASS / ALLPASS | 1 | MECHANICAL / SOURCE | `Connector_PinHeader_2.54mm:PinHeader_1x03_P2.54mm_Vertical` | Preserved connector family. Fit exact matching housing: JST-XH2.50mm is not Multicomp2.54mm. Headers/jumpers and panel controls must be checked separately. |
| J11 | HP BANK 1: 15/20/25 | 1 | MECHANICAL / SOURCE | `Connector_PinHeader_2.54mm:PinHeader_2x03_P2.54mm_Vertical` | Preserved connector family. Fit exact matching housing: JST-XH2.50mm is not Multicomp2.54mm. Headers/jumpers and panel controls must be checked separately. |
| J12 | HP BANK 2: 15/20/25 | 1 | MECHANICAL / SOURCE | `Connector_PinHeader_2.54mm:PinHeader_2x03_P2.54mm_Vertical` | Preserved connector family. Fit exact matching housing: JST-XH2.50mm is not Multicomp2.54mm. Headers/jumpers and panel controls must be checked separately. |
| J13 | AV HP: BYPASS / FILTER | 1 | MECHANICAL / SOURCE | `Connector_PinHeader_2.54mm:PinHeader_1x03_P2.54mm_Vertical` | Preserved connector family. Fit exact matching housing: JST-XH2.50mm is not Multicomp2.54mm. Headers/jumpers and panel controls must be checked separately. |
| J14 | COMMON HP: BYPASS / MODE | 1 | MECHANICAL / SOURCE | `Connector_PinHeader_2.54mm:PinHeader_1x03_P2.54mm_Vertical` | Preserved connector family. Fit exact matching housing: JST-XH2.50mm is not Multicomp2.54mm. Headers/jumpers and panel controls must be checked separately. |
| J15 | POLARITY 0 / 180 | 1 | MECHANICAL / SOURCE | `Connector_PinHeader_2.54mm:PinHeader_1x03_P2.54mm_Vertical` | Preserved connector family. Fit exact matching housing: JST-XH2.50mm is not Multicomp2.54mm. Headers/jumpers and panel controls must be checked separately. |
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
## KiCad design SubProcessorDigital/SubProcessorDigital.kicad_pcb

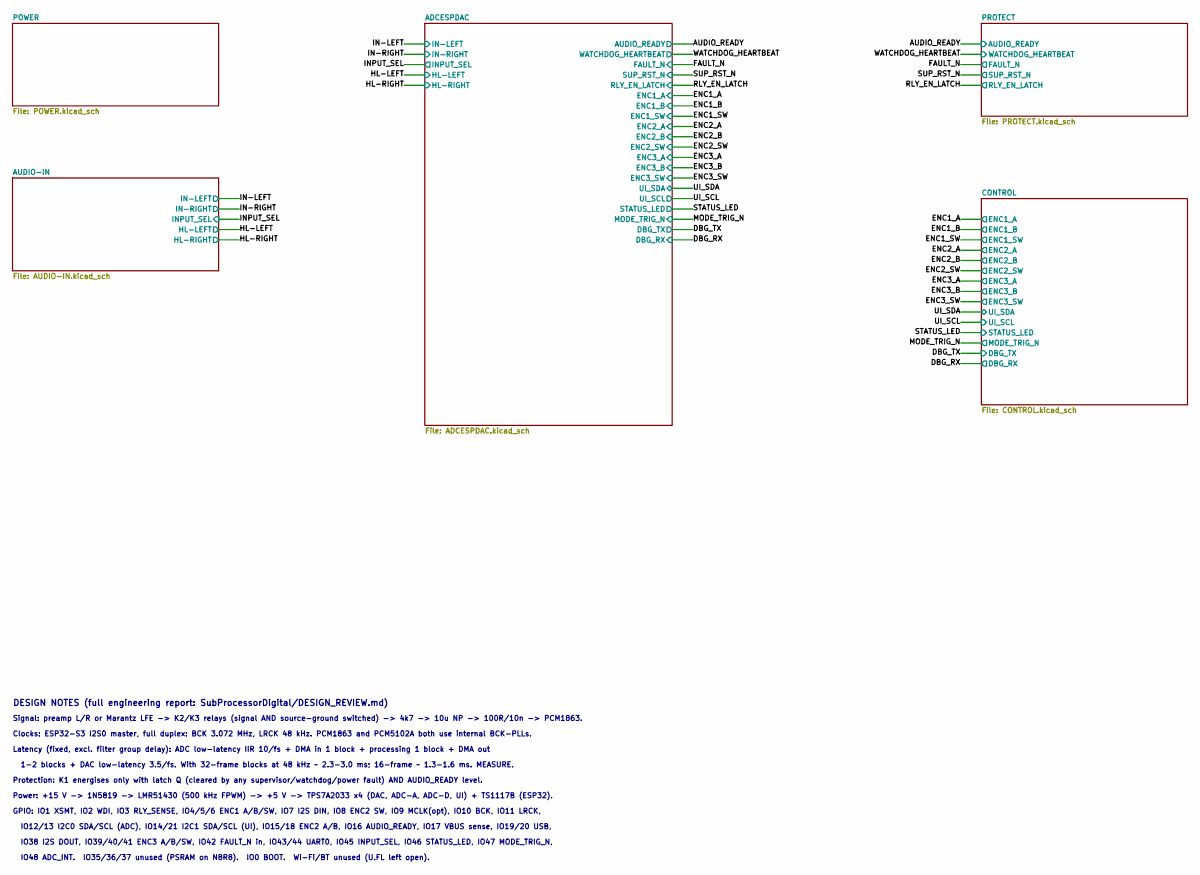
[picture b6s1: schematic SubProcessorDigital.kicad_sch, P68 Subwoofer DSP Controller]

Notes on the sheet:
DESIGN NOTES (full engineering report: SubProcessorDigital/DESIGN_REVIEW.md)
Power: +15 V -> 1N5819 -> LMR51430 (500 kHz FPWM) -> +5 V -> TPS7A2033 x4 (DAC, ADC-A, ADC-D, UI) + TS1117B (ESP32).
Clocks: ESP32-S3 I2S0 master, full duplex: BCK 3.072 MHz, LRCK 48 kHz. PCM1863 and PCM5102A both use internal BCK-PLLs.
1-2 blocks + DAC low-latency 3.5/fs. With 32-frame blocks at 48 kHz ~ 2.3-3.0 ms; 16-frame ~ 1.3-1.6 ms. MEASURE.
IO48 ADC_INT. IO35/36/37 unused (PSRAM on N8R8). IO0 BOOT. Wi-Fi/BT unused (U.FL left open).
IO38 I2S DOUT, IO39/40/41 ENC3 A/B/SW, IO42 FAULT_N in, IO43/44 UART0, IO45 INPUT_SEL, IO46 STATUS_LED, IO47 MODE_TRIG_N,
Latency (fixed, excl. filter group delay): ADC low-latency IIR 10/fs + DMA in 1 block + processing 1 block + DMA out
Protection: K1 energises only with latch Q (cleared by any supervisor/watchdog/power fault) AND AUDIO_READY level.
GPIO: IO1 XSMT, IO2 WDI, IO3 RLY_SENSE, IO4/5/6 ENC1 A/B/SW, IO7 I2S DIN, IO8 ENC2 SW, IO9 MCLK(opt), IO10 BCK, IO11 LRCK,
IO12/13 I2C0 SDA/SCL (ADC), IO14/21 I2C1 SDA/SCL (UI), IO15/18 ENC2 A/B, IO16 AUDIO_READY, IO17 VBUS sense, IO19/20 USB,
Signal: preamp L/R or Marantz LFE -> K2/K3 relays (signal AND source-ground switched) -> 4k7 -> 10u NP -> 100R/10n -> PCM1863.
